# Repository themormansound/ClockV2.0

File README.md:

# ClockV2.0
An arduino nano based Euro module for making clock code come to life

10ish Volt outputs on digital pins 8,9,10 and 11

4 pots connected to A1, A2, A3 and A4

2 led tactile switches on D2 and D3 (interrupt pins on nano) leds hang off pins D4 and D5

Included is some sample code

If you go ahead and build this, ping me and let me know. 

Build notes, Make sure you solder in the arduino LAST, otherwise you wont be able to do the switches or the pair of components underneath.

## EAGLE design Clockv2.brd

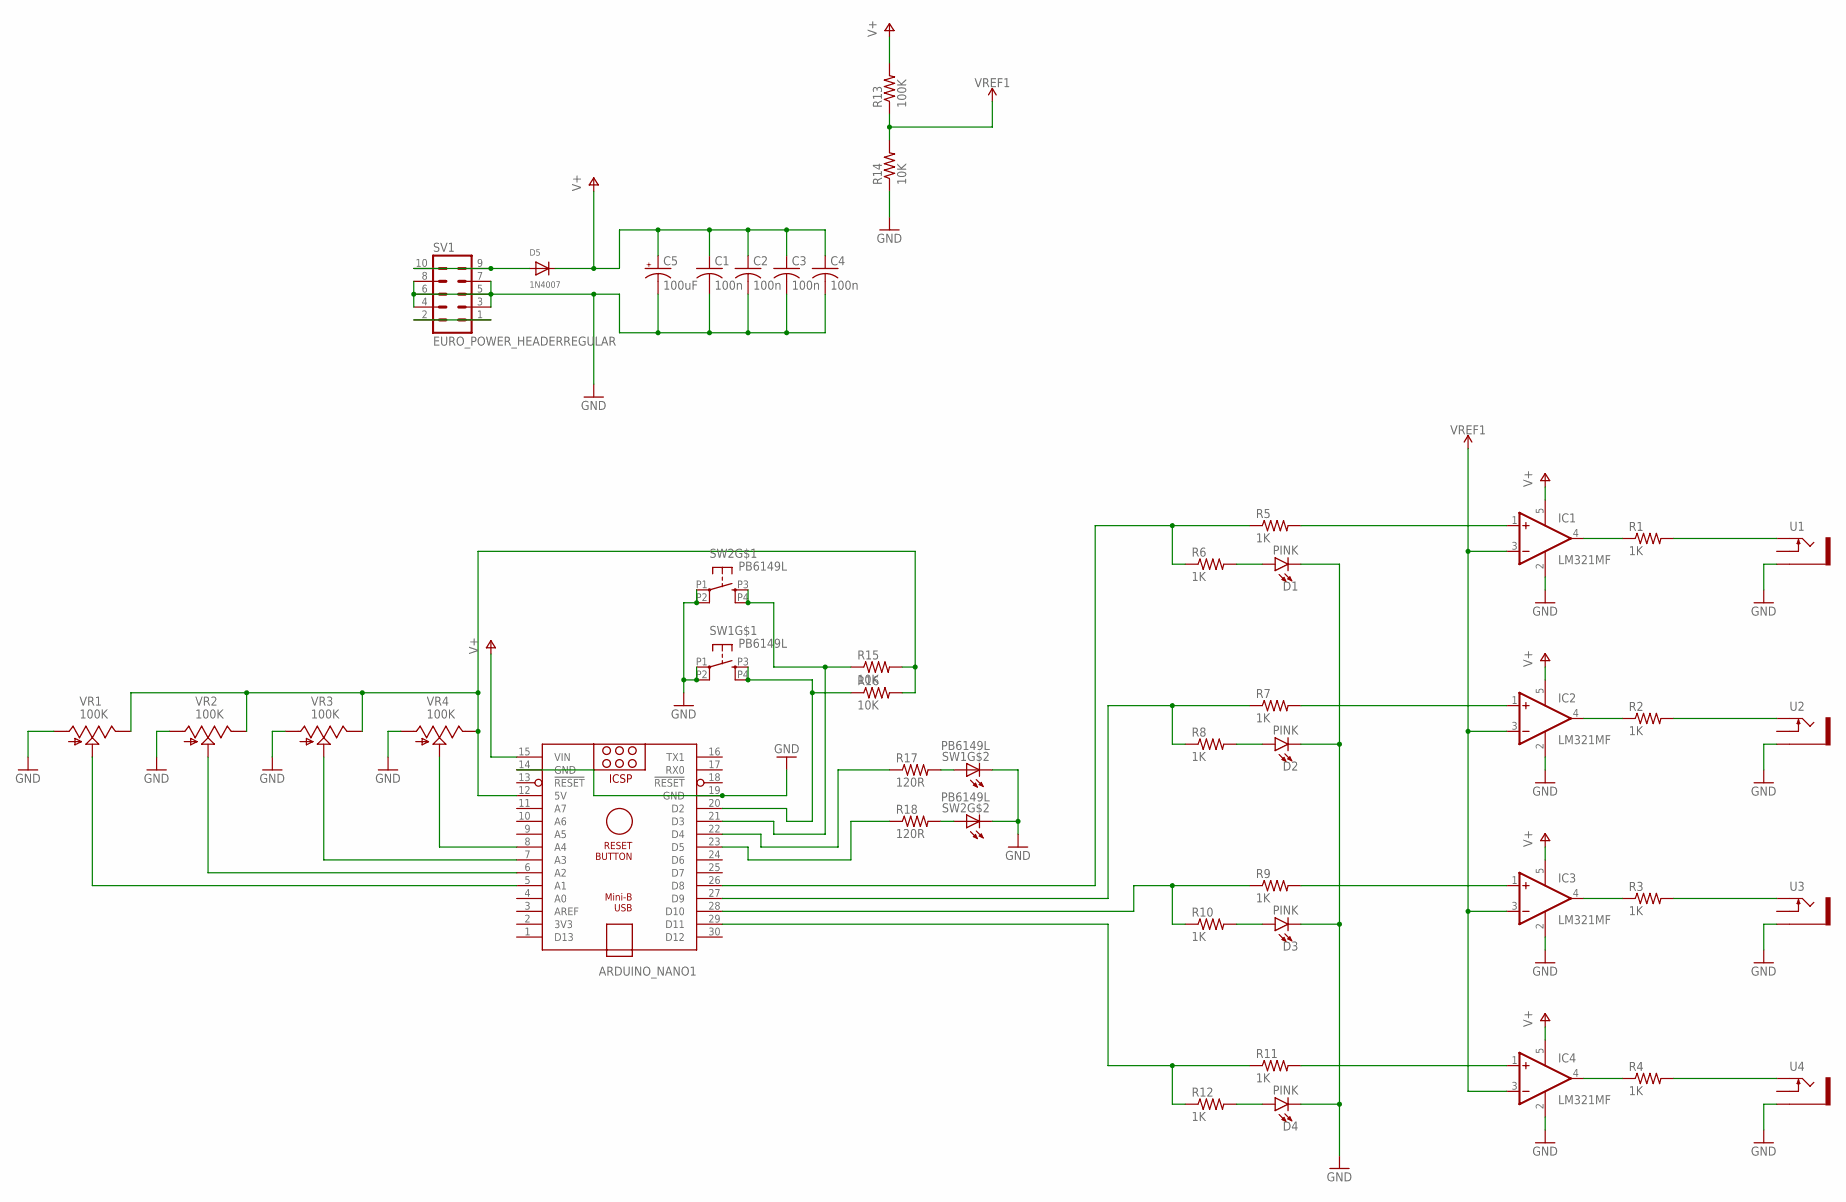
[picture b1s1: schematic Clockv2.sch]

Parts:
ARDUINO_NANO1: ARDUINO_NANO
C1, C2, C3, C4: 100n; C0805K
C5: 100uF; PANASONIC_B
D1, D2, D3, D4: PINK; LED_3MM
D5: 1N4007; SOD-123
IC1, IC2, IC3, IC4: LM321MF; SOT23-5
R1, R2, R3, R4, R5, R6, R7, R8, R9, R10, R11, R12: 1K; R0805
R13: 100K; R0805
R14, R15, R16: 10K; R0805
R17, R18: 120R; R0805
SV1: EURO_POWER_HEADERREGULAR; EURO_POWER_HEADER
SW1, SW2: PB6149L
U1, U2, U3, U4: THONKICONNNEW; WQP-PJ301M-12_JACK
VR1, VR2, VR3, VR4: 100K; 9MM_SNAP-IN_POT

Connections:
GND: ARDUINO_NANO1.14 (GND), ARDUINO_NANO1.19 (GND), C1.2, C2.2, C3.2, C4.2, C5.-, D1.K (C), D2.K (C), D3.K (C), D4.K (C), IC1.2 (V-), IC2.2 (V-), IC3.2 (V-), IC4.2 (V-), R14.1, SV1.3, SV1.4, SV1.5, SV1.6, SV1.7, SV1.8, SW1.L2 (C), SW1.P1, SW1.P2 (P1), SW2.L2 (C), SW2.P1, SW2.P2 (P1), U1.P$3_SLEEVE (SLEEVE), U2.P$3_SLEEVE (SLEEVE), U3.P$3_SLEEVE (SLEEVE), U4.P$3_SLEEVE (SLEEVE), VR1.1 (A), VR2.1 (A), VR3.1 (A), VR4.1 (A)
unnamed: IC1.4 (OUT), R1.1
unnamed: IC2.4 (OUT), R2.1
unnamed: IC3.4 (OUT), R3.1
unnamed: IC4.4 (OUT), R4.1
unnamed: R1.2, U1.P$1_TIP (TIP)
unnamed: R2.2, U2.P$1_TIP (TIP)
unnamed: R3.2, U3.P$1_TIP (TIP)
unnamed: R4.2, U4.P$1_TIP (TIP)
unnamed: ARDUINO_NANO1.28 (D10), R9.1, R10.1
unnamed: ARDUINO_NANO1.26 (D8), R5.1, R6.1
unnamed: ARDUINO_NANO1.27 (D9), R7.1, R8.1
unnamed: ARDUINO_NANO1.29 (D11), R11.1, R12.1
unnamed: D1.A, R6.2
unnamed: ARDUINO_NANO1.12 (5V), R15.2, R16.2, VR1.3 (E), VR2.3 (E), VR3.3 (E), VR4.3 (E)
unnamed: ARDUINO_NANO1.20 (D2), R16.1, SW1.P3 (S), SW1.P4 (S1)
unnamed: D2.A, R8.2
unnamed: ARDUINO_NANO1.21 (D3), R15.1, SW2.P3 (S), SW2.P4 (S1)
unnamed: IC2.1 (+IN), R7.2
unnamed: IC1.1 (+IN), R5.2
unnamed: IC3.1 (+IN), R9.2
unnamed: D5.A, SV1.9, SV1.10
unnamed: D3.A, R10.2
unnamed: ARDUINO_NANO1.8 (A4), VR4.2 (S)
unnamed: IC4.1 (+IN), R11.2
unnamed: D4.A, R12.2
unnamed: ARDUINO_NANO1.7 (A3), VR3.2 (S)
unnamed: ARDUINO_NANO1.6 (A2), VR2.2 (S)
unnamed: ARDUINO_NANO1.5 (A1), VR1.2 (S)
unnamed: R17.2, SW1.L1 (A)
unnamed: R18.2, SW2.L1 (A)
unnamed: ARDUINO_NANO1.22 (D4), R17.1
unnamed: ARDUINO_NANO1.23 (D5), R18.1
unnamed: SV1.1, SV1.2
V+: ARDUINO_NANO1.15 (VIN), C1.1, C2.1, C3.1, C4.1, C5.+, D5.C, IC1.5 (V+), IC2.5 (V+), IC3.5 (V+), IC4.5 (V+), R13.2
VREF1: IC1.3 (-IN), IC2.3 (-IN), IC3.3 (-IN), IC4.3 (-IN), R13.1, R14.2

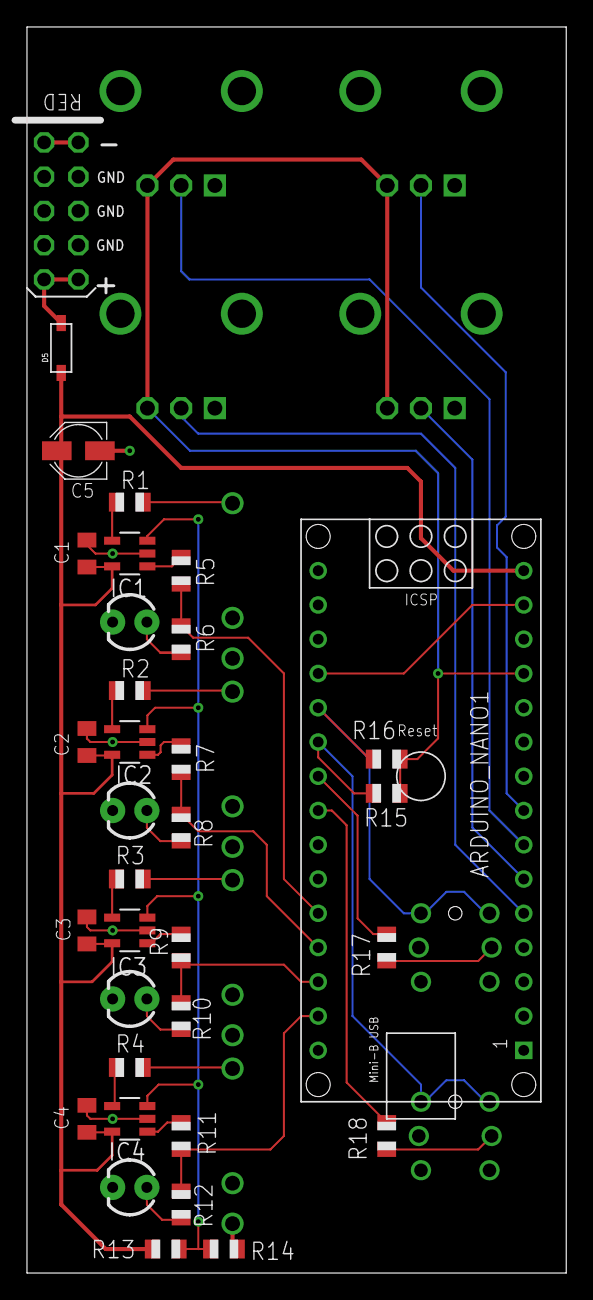
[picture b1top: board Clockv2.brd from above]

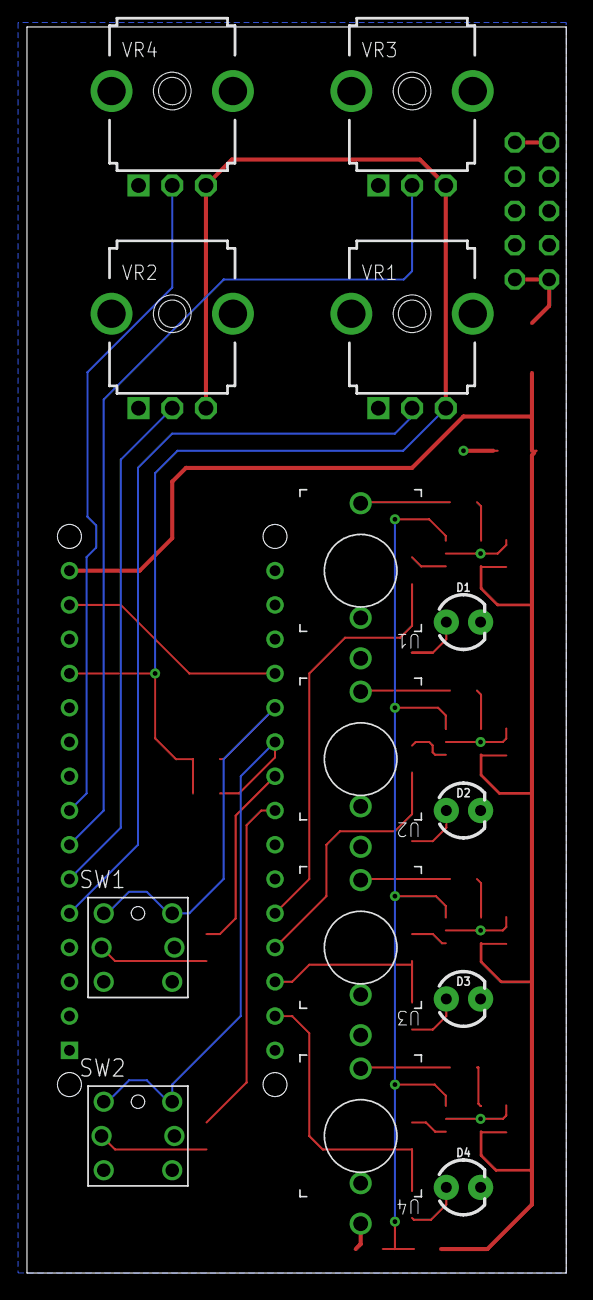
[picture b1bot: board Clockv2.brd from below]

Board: 2 copper layers, 40.0 x 92.4 mm, 44 parts (14 on the bottom side), 36 nets.

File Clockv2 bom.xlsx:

Comment | Designator | Footprint | Descripton
1K | R1 R2 R3 R4 R5 R6 R7 R8 R9 R10 R11 R12 | R0805 | 1K Ohm, 1% 0805 resistors
10K | R14 R15 R16 | R0805 | 10K Ohm, 1% 0805 resistors
100K | R13 | R0805 | 100K Ohm, 1% 0805 resistors
120R | R17 R18 | R0805 | 120 Ohm, 1% 0805 resistors
100n | C1 C2 C3 C4 | C0805K | 100nF, 50v 0805 capacitors
100uF | C5 | PANASONIC_B | 100uF, 50v 5mmx5mm electrolytic capacitors
LM321MF | IC1 IC2 IC3 IC4 | SOT23-5 | LM321MF General Purpose Amplifier 1 Circuit SOT-23-5
1N4007 | D5 | SOD-123 | any generic power diode will work, I use 1N4148W-7F
B100K | VR1 VR2 VR3 VR4 | RK09 | 9mm snap in style, alps RK09 or similar
SW1 SW2 | PB6149L | PB6149L | https://www.tme.eu/en/details/pb6149l-1/keypad-switches/high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
POWER | SV1 | 10 PIN HEADER
LED | D1 D2 D3 D4 | 3mm LED | any 3mm led will work here. (you could use 5mm ones too, but you'll have to dri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
JACK | U1 U2 U3 U4 | Thonkicon Jack | Standard thonkicon style jacks (WQP518MA) get em from Aliexpress
AN | ARDUINO_NANO | Arduino Nano | Arduino nano board

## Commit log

2023-03-27 Rename Clock.ino to ClockV2.ino
2024-12-06 Add files via upload
    Added BOM

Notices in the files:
parts and their libraries:
SparkFun-LED: Licensing: Creative Commons ShareAlike 4.0 International - https://creativecommons.org/licenses/by-sa/4.0
